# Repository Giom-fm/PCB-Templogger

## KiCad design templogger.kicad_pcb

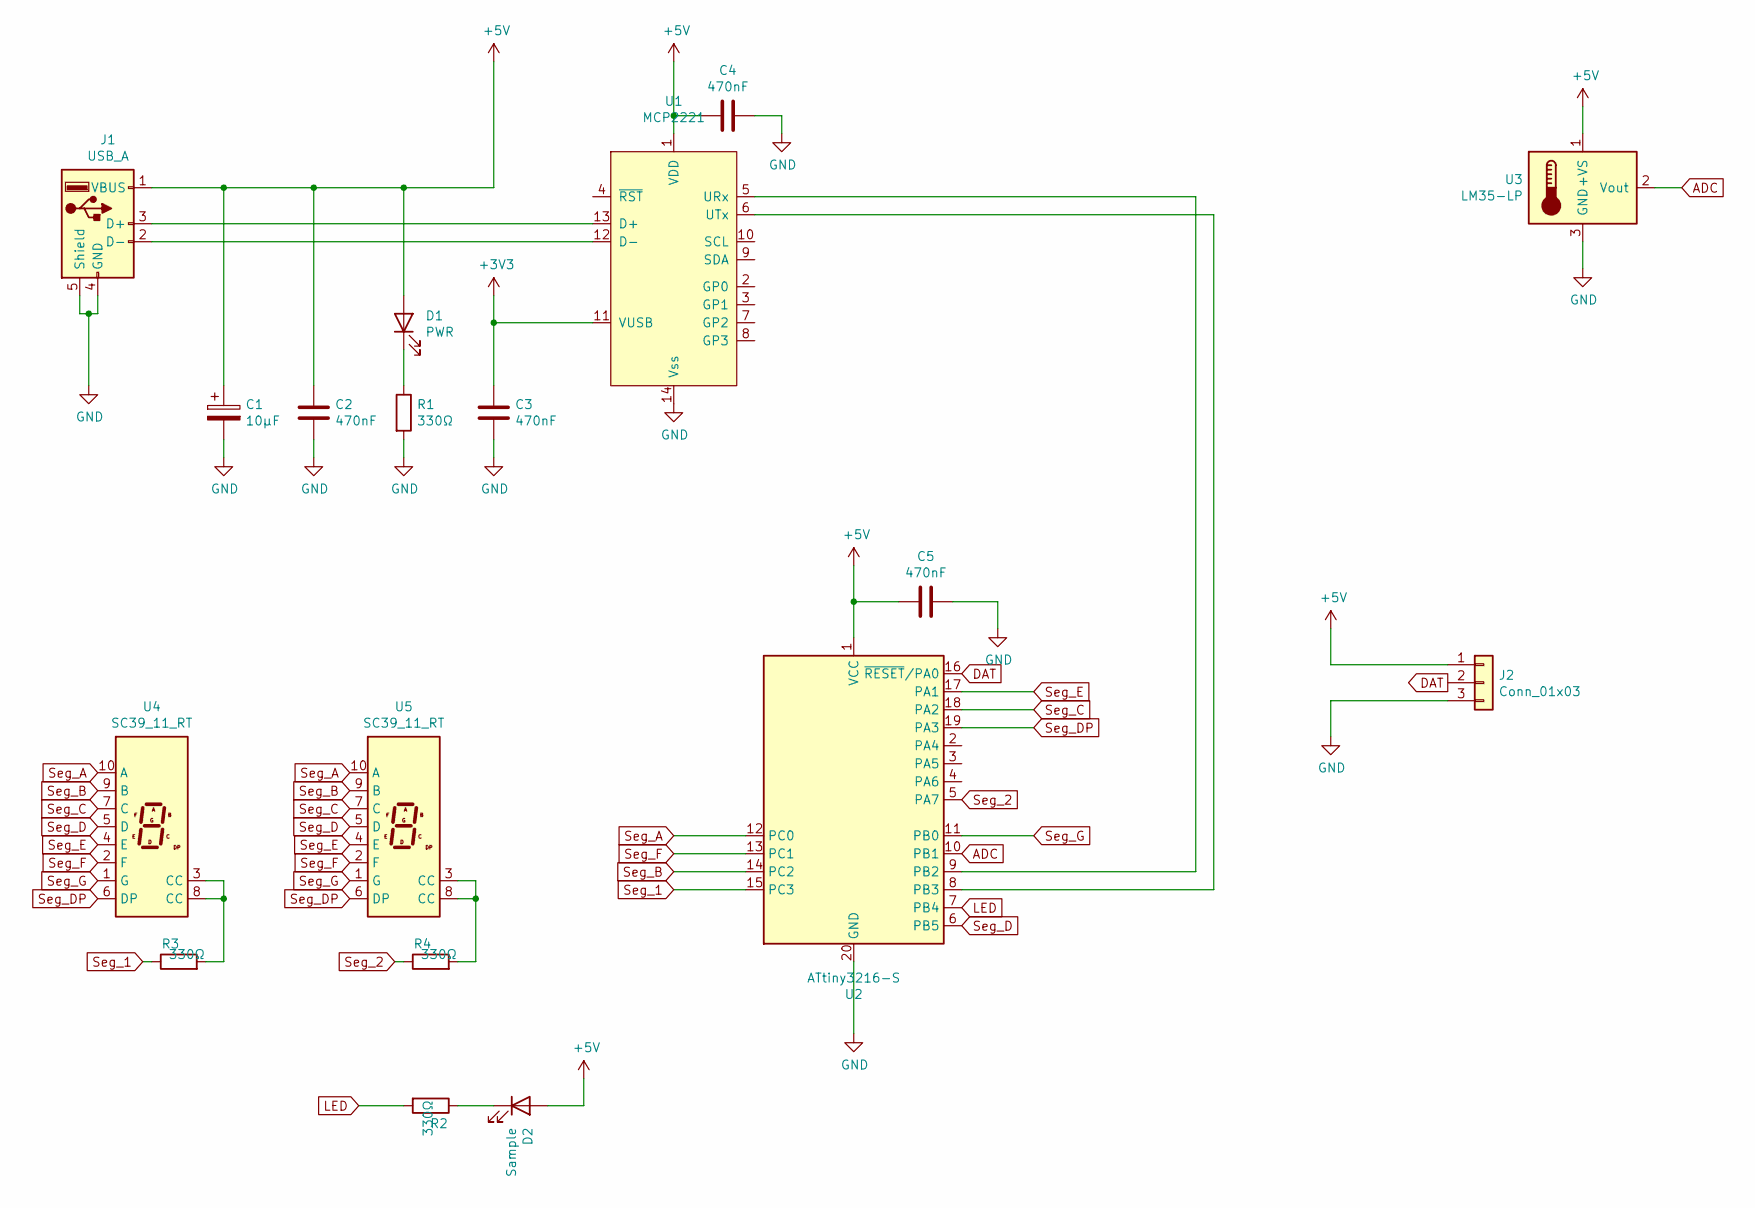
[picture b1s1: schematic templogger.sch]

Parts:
C1: 10µF; C_Disc_D4.3mm_W1.9mm_P5.00mm
C2, C3, C4, C5: 470nF; C_Disc_D4.3mm_W1.9mm_P5.00mm
D1: PWR; LED_D5.0mm
D2: Sample; LED_D5.0mm
J1: USB_A; USB_AWF
J2: Conn_01x03; PinHeader_1x03_P2.54mm_Vertical
R1, R2, R3, R4: 330Ω; R_Axial_DIN0207_L6.3mm_D2.5mm_P2.54mm_Vertical
U1: MCP2221; SOIC-14_3.9x8.7mm_P1.27mm
U2: ATtiny3216-S; SOIC-20W_7.5x12.8mm_P1.27mm
U3: LM35-LP; TO-92
U4, U5: SC39_11_RT; SC39-11_RT_small

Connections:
+3V3: C3.1, U1.11 (VUSB)
+5V: C1.1, C2.1, C4.2, C5.2, D1.2 (A), D2.2 (A), J1.1 (VBUS), J2.1, U1.1 (VDD), U2.1 (VCC), U3.1 (+VS)
ADC: U2.10 (PB1), U3.2 (Vout)
DAT: J2.2, U2.16 (~RESET~/PA0)
GND: C1.2, C2.2, C3.2, C4.1, C5.1, J1.4 (GND), J1.5 (Shield), J2.3, R1.2, U1.14 (Vss), U2.20 (GND), U3.3 (GND)
LED: R2.2, U2.7 (PB4)
unnamed: D1.1 (K), R1.1
unnamed: D2.1 (K), R2.1
unnamed: J1.2 (D-), U1.12 (D-)
unnamed: J1.3 (D+), U1.13 (D+)
unnamed: R3.2, U4.3 (CC), U4.8 (CC)
unnamed: R4.2, U5.3 (CC), U5.8 (CC)
unnamed: U1.5 (URx), U2.9 (PB2)
unnamed: U1.6 (UTx), U2.8 (PB3)
Seg_1: R3.1, U2.15 (PC3)
Seg_2: R4.1, U2.5 (PA7)
Seg_A: U2.12 (PC0), U4.10 (A), U5.10 (A)
Seg_B: U2.14 (PC2), U4.9 (B), U5.9 (B)
Seg_C: U2.18 (PA2), U4.7 (C), U5.7 (C)
Seg_D: U2.6 (PB5), U4.5 (D), U5.5 (D)
Seg_DP: U2.19 (PA3), U4.6 (DP), U5.6 (DP)
Seg_E: U2.17 (PA1), U4.4 (E), U5.4 (E)
Seg_F: U2.13 (PC1), U4.2 (F), U5.2 (F)
Seg_G: U2.11 (PB0), U4.1 (G), U5.1 (G)

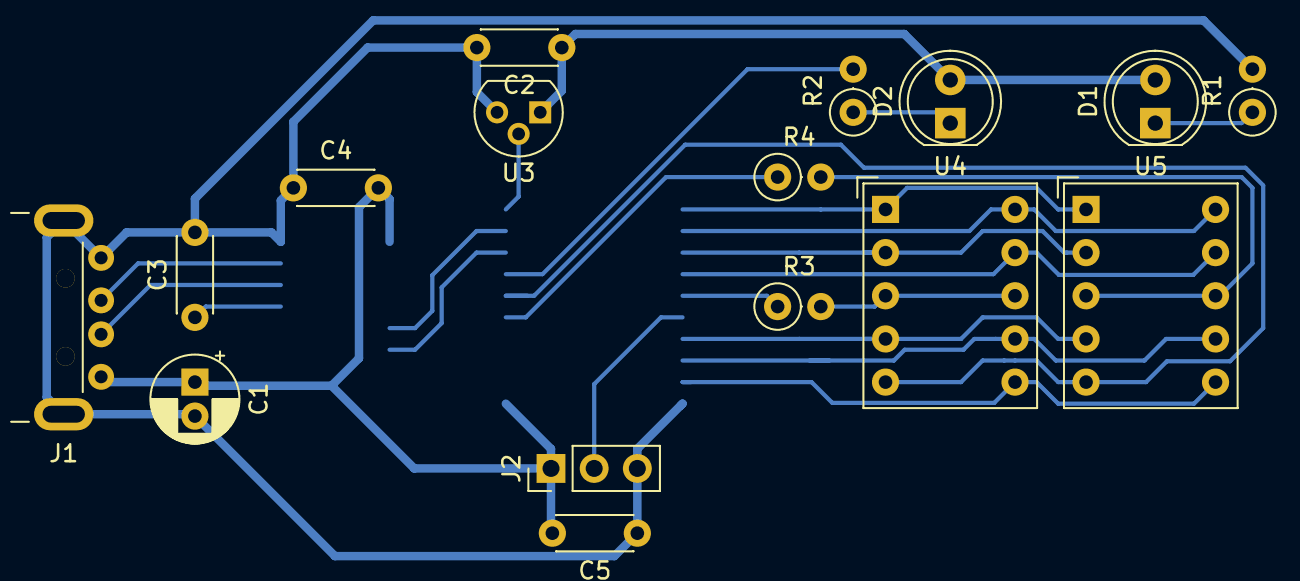
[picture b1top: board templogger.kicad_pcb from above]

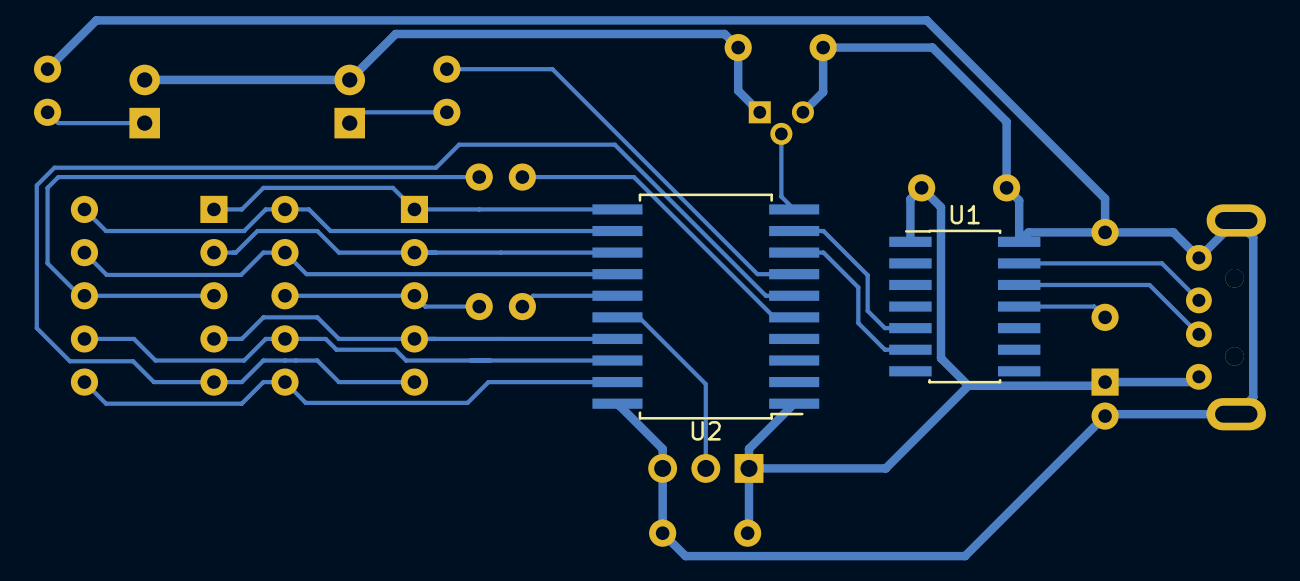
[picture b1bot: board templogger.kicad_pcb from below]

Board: 2 copper layers, 18 parts (2 on the bottom side), 24 nets.

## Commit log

2020-05-20 init
2020-05-20 Add Readme
2020-05-24 First PCB Layout
2020-09-09 Optimize routing. not done...
